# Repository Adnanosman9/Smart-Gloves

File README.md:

# BdSL Translator Glove

The **BdSL Translator Glove** is a wearable device designed to translate BdSL into words without any camera setup.

## How It Works

*   **Sensors:** The glove tracks movement using bend sensors or custom, flexible 3D-printed tpu that changes its voltage when your fingers move.
*   **Brain:** An esp module tracks exactly how your hand moves and tilts, turns those gestures into data, and sends the translated speech to a device.

## Recent Design Updates

*   **Lower Cost:** Switched to smaller sensors, cutting the hardware budget down to about $100 for a full two-handed setup.
*   **Better Fit:** Upgraded the design from a clunky plastic box to form-fitting, flexible finger guides that follow the shape of the hand.

## Finger Guides

Shoutout to [zackfreedman](https://www.thingiverse.com/thing:1606915) for the original parametric ring glove concept that inspired this design. You can grab my modified STL [here](https://github.com/Adnanosman9/Smart-Gloves/blob/main/CAD%20for%20flex%20sensor/Ring_Glove_Parametric.stl).

Instead of messing around with messy glues or tape, each finger uses a 3D-printed TPU channel segment where the sensor just slides right in and locks mechanically. I split these into two sizes:
*   **Long:** For your index, middle, and ring fingers.
*   **Short:** Form-fitted for the thumb and pinky to match their shorter lengths and natural joint angles.

Any standard FDM printing service can easily run these off in white TPU filament.

---

## PCB Design

I put together a compact wrist hub in KiCad to keep the electronics tidy. A few design choices:

*   **Brain:** The **XIAO ESP32-C3** was a no-brainer. It's incredibly small, handles Bluetooth LE natively, and has just enough ADC pins for all 5 fingers.
*   **Hardware Filtering:** Because flex sensors have a pretty high impedance, I added a **47kΩ voltage divider** on every sensor input to keep readings steady. I also threw in **0.1µF decoupling capacitors** along the sensor traces to smooth out some electrical noise I ran into during early testing.

The KiCad DRC checked out cleanly with 0 errors (just a few minor silkscreen overlap warnings that won't disrupt manufacturing).

**Schematic:**

**PCB Layout:**

---

## Enclosure

The wrist housing was designed in Fusion 360 to keep the pcb safe. 

### Get the CAD assembly [here](https://github.com/Adnanosman9/Smart-Gloves/blob/main/CAD%20for%20flex%20sensor/assembly.f3z)

---

## Alternative of commercial Sensors

Here is an alter for commercial sensors for cost optimization. 

*   [Middle, Index, & Ring fingers](https://github.com/Adnanosman9/Smart-Gloves/blob/main/CAD_3d%20printed%20sensor/Mid%20fingers-TPU.f3z)
*   [Pinky & Thumb fingers](https://github.com/Adnanosman9/Smart-Gloves/blob/main/CAD_3d%20printed%20sensor/Pinky_Thumb_finger--TPU.f3z)

---

## Firmware Status

**Just a quick heads up:** I haven't been able to run this code on physical hardware yet. It's highly likely there are some I2C pin configuration mismatches, flipped GPIO definitions, or sensor initialization bugs waiting to happen on the first boot. Please double-check your schematic assignments against your software configuration before flashing! 

## Bill of Materials

You can view the full parts list in the [BOM file here](bom/BOM.csv).

> GitHub [@Adnanosman](https://github.com/Adnanosman9)

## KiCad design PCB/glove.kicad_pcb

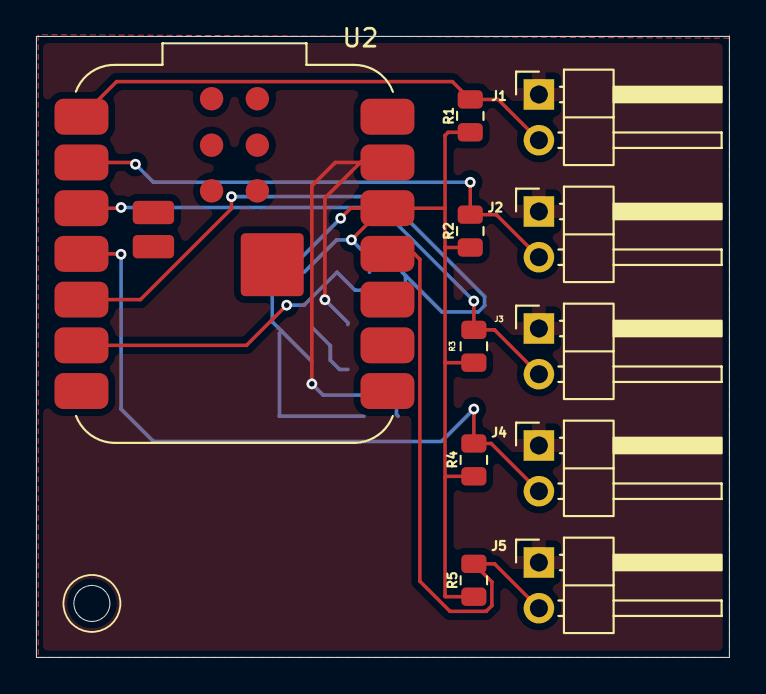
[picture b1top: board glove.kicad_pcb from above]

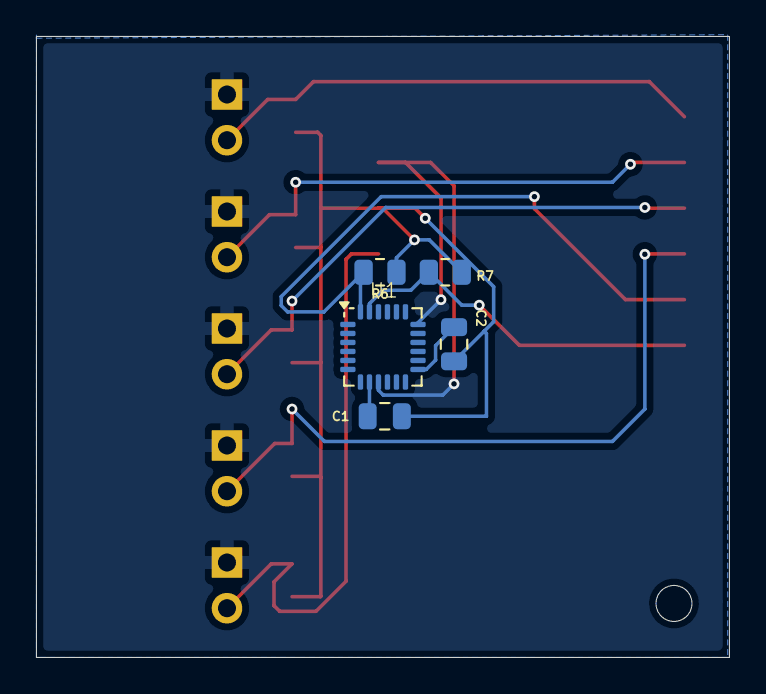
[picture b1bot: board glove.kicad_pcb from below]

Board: 2 copper layers, 38.5 x 34.5 mm, 16 parts (5 on the bottom side), 11 nets.

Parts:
C1, C2: 0.1uf; C_0805_2012Metric
J1, J2, J3, J4, J5: Conn_01x02_Pin; PinHeader_1x02_P2.54mm_Horizontal
R1, R2, R3, R4, R5: 47k; R_0805_2012Metric
R6, R7: 4.7k; R_0805_2012Metric
U1: MPU-6050; InvenSense_QFN-24_4x4mm_P0.5mm
U2: XIAO-ESP32-C3-SMD; MCU_Seeed_ESP32C3

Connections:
+3V3: C1.1, C2.1, R1.1, R2.1, R3.1, R4.1, R5.1, R6.1, R7.1, U2.12 (3V3)
/IMU_SCL: R7.2, U1.23 (SCL), U2.6 (GPIO7_D5_SCL)
/IMU_SDA: R6.2, U1.24 (SDA), U2.5 (GPIO6_D4_SDA)
/sensor_1: J1.2, R1.2, U2.1 (GPIO2_A0_D0)
/sensor_2: J2.2, R2.2, U2.2 (GPIO3_A1_D1)
/sensor_3: J3.2, R3.2, U2.3 (GPIO4_A2_D2)
/sensor_4: J4.2, R4.2, U2.4 (GPIO5_A3_D3)
/sensor_5: J5.2, R5.2, U2.11 (GPIO10_D10_MOSI)
GND: J1.1, J2.1, J3.1, J4.1, J5.1, U1.9 (AD0), U1.18 (GND), U2.13 (GND)
unnamed: C2.2, U1.13 (VDD)
unnamed: C1.2, U1.8 (VLOGIC)

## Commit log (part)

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2026-02-20 Create BOM
2026-03-18 Full Update
